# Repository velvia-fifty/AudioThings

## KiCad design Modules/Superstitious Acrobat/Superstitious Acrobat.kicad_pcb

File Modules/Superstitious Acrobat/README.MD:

# Superstitious Acrobat (and friends)

How many multiples give you the freedom to configure them how you want? OK but do they have *range*? I'm talking 1:13 to 14:0 range, how many 0 port multiples do you even have right now!?

## What problem are you trying to solve?

Consider the lede buried; I wanted a pair of FX loops and a compact way to shove a **FUCKTON** of signals into them. I also want the ability to touch those signals, not inappropriately but in the kind of way that garners stern looks of disapproval.

### Superstitious Acrobat

The first module is incredibly dense, your uncle's friend Dave from Facebook dense, A pair of 7 Stereo Jacks that you can slice, dice, and turn tricks with dense. Sure, you have to lay down solder blobs, and sure, you might have to think before you plug, but consider this:

Take a stereo signal, now give me two copies of that, and then a pair of each channel on the tip. Then take a second mono signal, split that six ways, and maybe throw the right channel of the other signal on the right side of half of those.

Why would you need to do that? 🤷‍♀️, but now you can.

### Midnight Gymnast

Wanna see me do some unorthodox splits?

Fill me up with a two pairs of stereo jacks (that's eight signals if you've lost count) and flip and twist until I make the sounds you like. Flip between each half of each pair, then blend each channel of those jacks.

Did this description need to be so passive aggressively sexual? 🍆💦☔️

### Full Send

Oh right, the FX loops, did I mention that there's a flat-flex cable so you can route the multiple right to it, or whatever - the interface port is standardized... 'n junk.

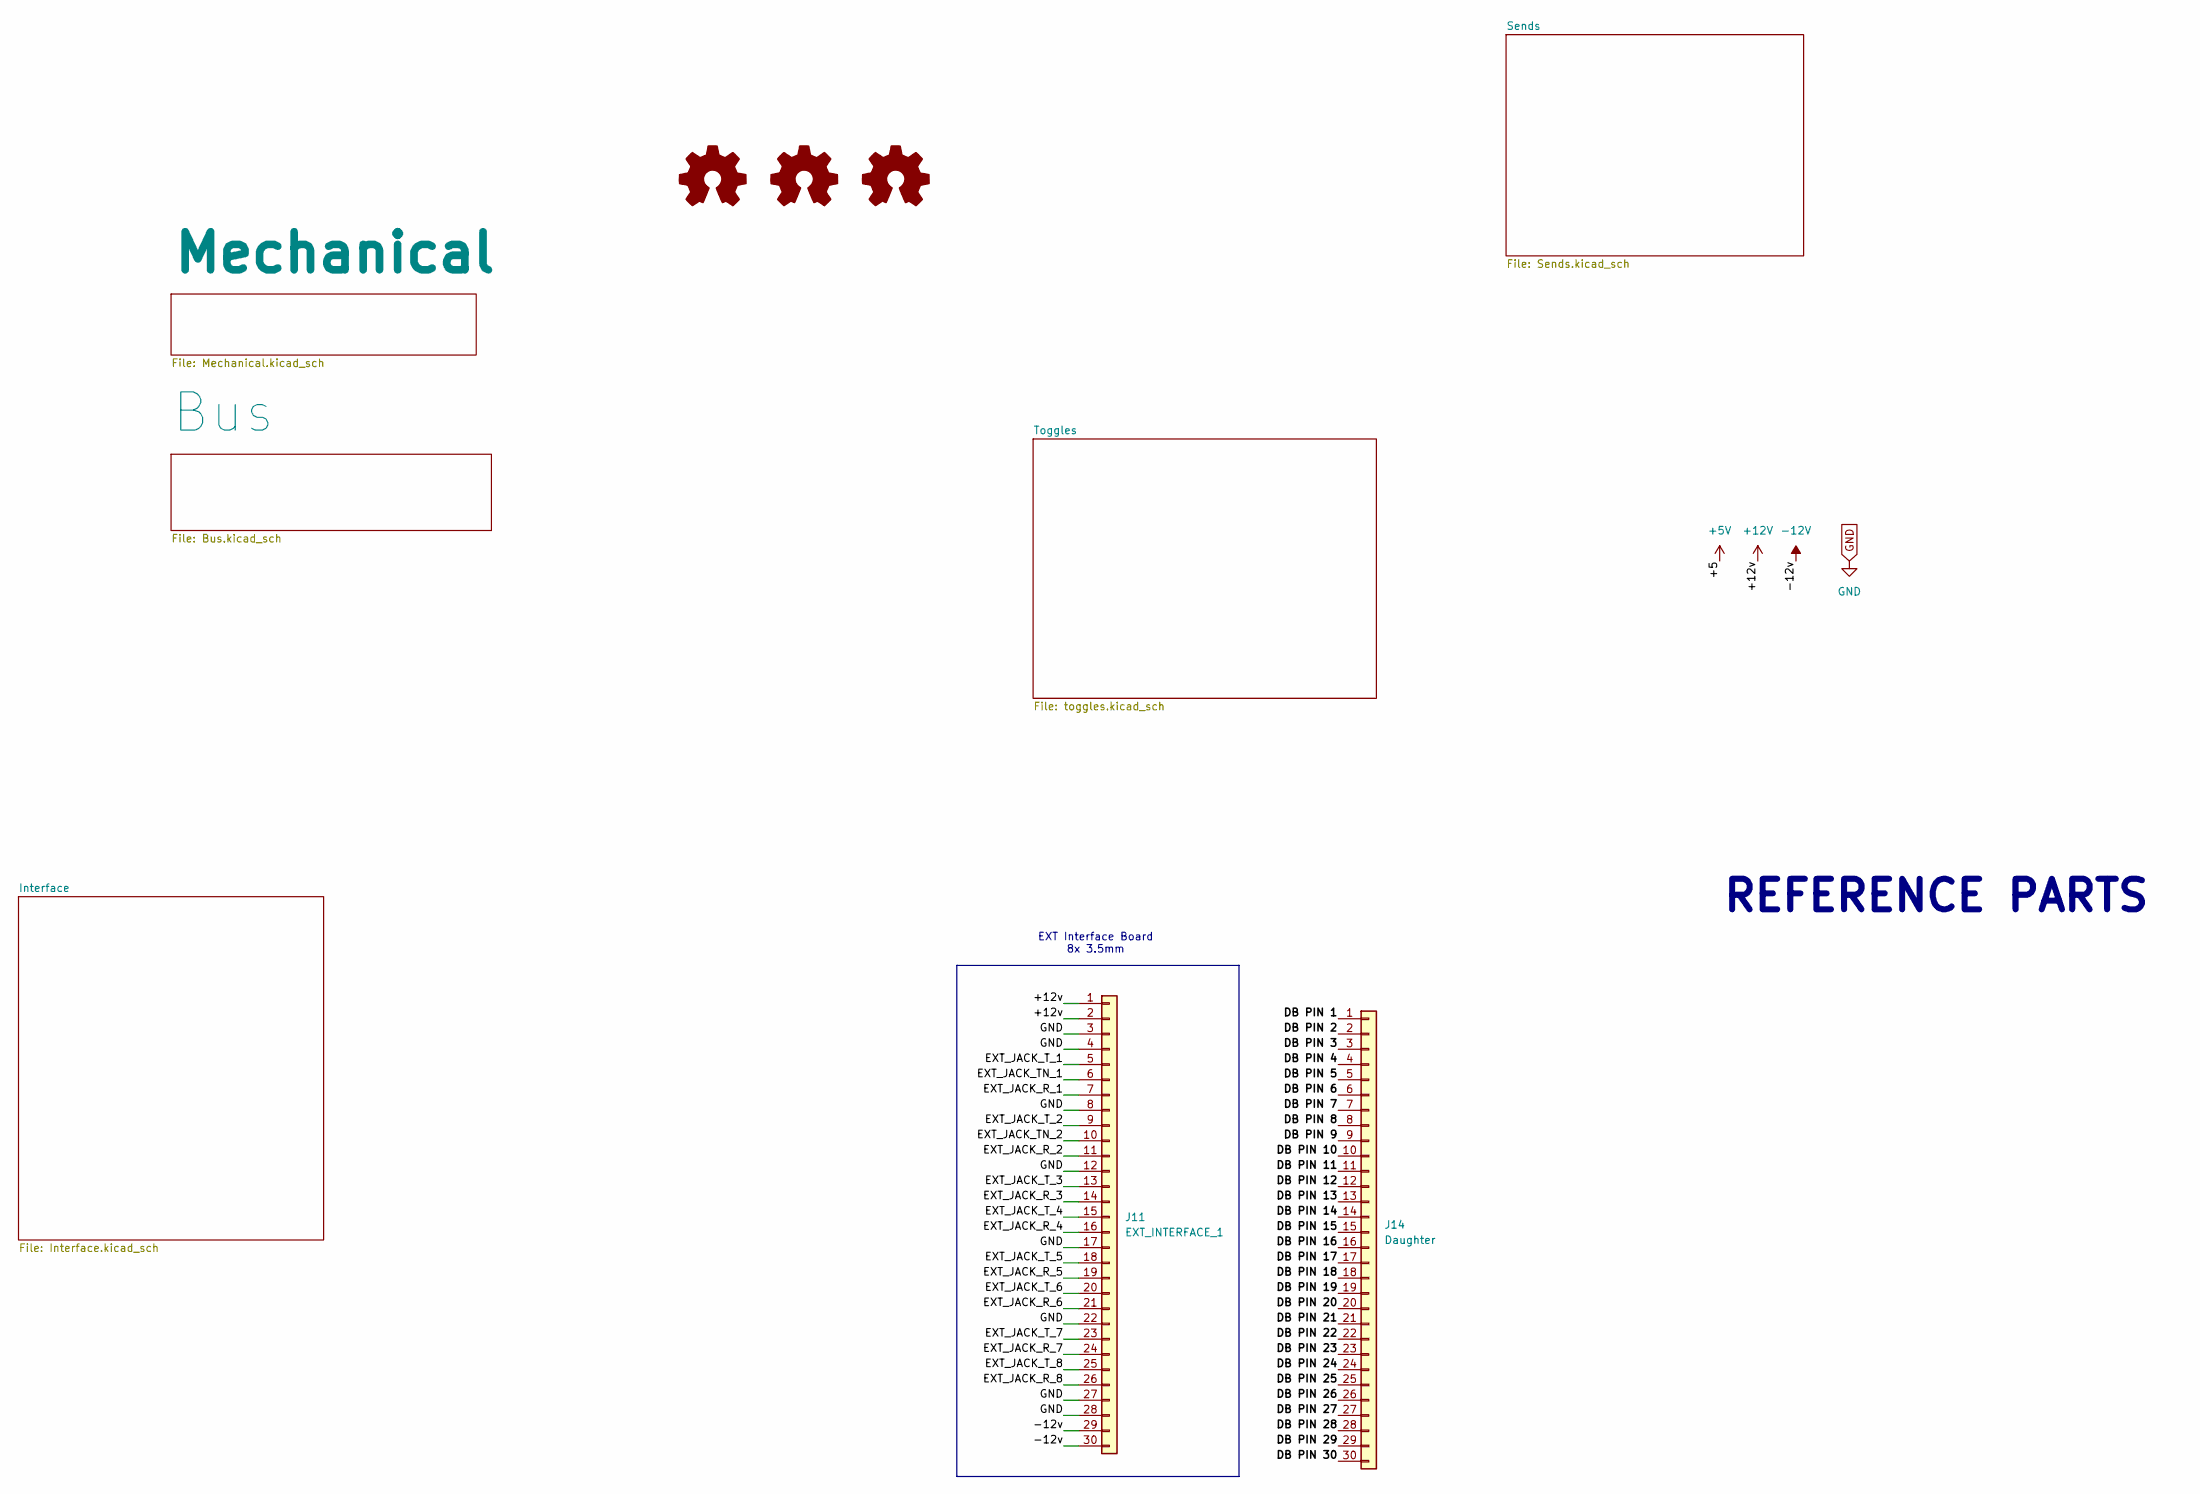
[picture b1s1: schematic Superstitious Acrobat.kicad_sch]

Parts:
J11: EXT_INTERFACE_1; AMPHENOL_SFV30R-4STE1HLF - FFC - 30 RA
J14: Daughter; AMPHENOL_SFV30R-4STE1HLF - FFC - 30 RA

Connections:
+12V: J11.1, J11.2
-12V: J11.29, J11.30
/EXT_JACK_R_1: J11.7
/EXT_JACK_R_2: J11.11
/EXT_JACK_R_3: J11.14
/EXT_JACK_R_4: J11.16
/EXT_JACK_R_5: J11.19
/EXT_JACK_R_6: J11.21
/EXT_JACK_R_7: J11.24
/EXT_JACK_R_8: J11.26
/EXT_JACK_TN_1: J11.6
/EXT_JACK_TN_2: J11.10
/EXT_JACK_T_1: J11.5
/EXT_JACK_T_2: J11.9
/EXT_JACK_T_3: J11.13
/EXT_JACK_T_4: J11.15
/EXT_JACK_T_5: J11.18
/EXT_JACK_T_6: J11.20
/EXT_JACK_T_7: J11.23
/EXT_JACK_T_8: J11.25
GND: J11.3, J11.4, J11.8, J11.12, J11.17, J11.22, J11.27, J11.28; also elsewhere on the board

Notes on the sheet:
REFERENCE PARTS
EXT Interface Board 8x 3.5mm

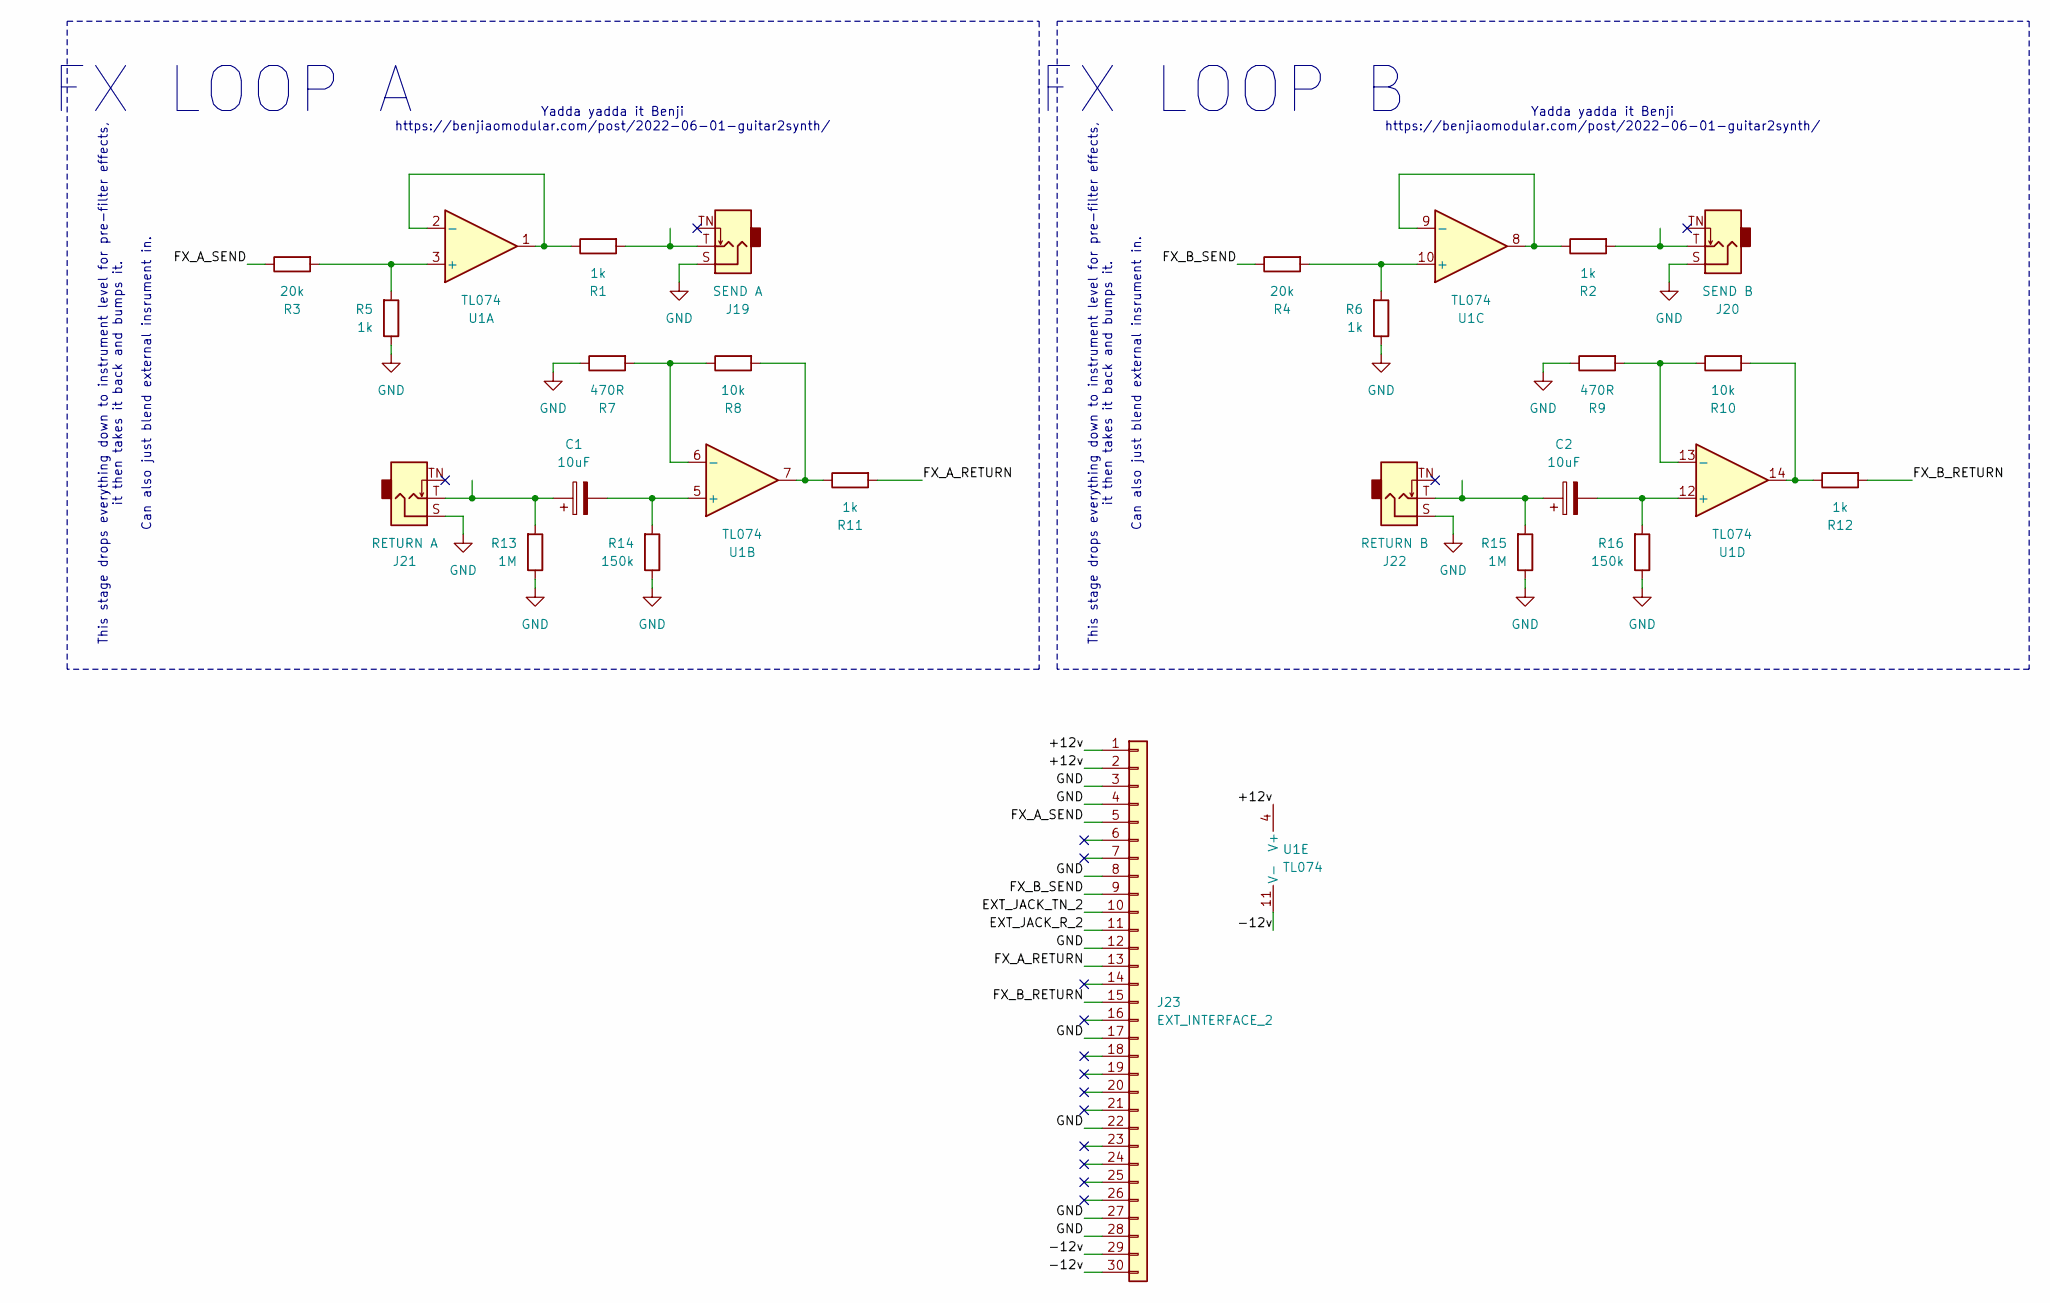
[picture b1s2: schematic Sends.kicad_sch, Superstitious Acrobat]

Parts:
C1, C2: 10uF; CP_Elec_5x5.4
J19: SEND A; Quarter Inch
J20: SEND B; Quarter Inch
J21: RETURN A; Quarter Inch
J22: RETURN B; Quarter Inch
J23: EXT_INTERFACE_2; AMPHENOL_SFV30R-4STE1HLF - FFC - 30 RA
R1, R2, R5, R6, R11, R12: 1k; R_0805_2012Metric_Pad1.20x1.40mm_HandSolder
R3, R4: 20k; R_0805_2012Metric_Pad1.20x1.40mm_HandSolder
R7, R9: 470R; R_0805_2012Metric_Pad1.20x1.40mm_HandSolder
R8, R10: 10k; R_0805_2012Metric_Pad1.20x1.40mm_HandSolder
R13, R15: 1M; R_0805_2012Metric_Pad1.20x1.40mm_HandSolder
R14, R16: 150k; R_0805_2012Metric_Pad1.20x1.40mm_HandSolder
U1: TL074; TSSOP-14_4.4x5mm_P0.65mm

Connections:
/Sends/+12v: J23.1, J23.2, U1.4 (V+)
/Sends/-12v: J23.29, J23.30, U1.11 (V-)
/Sends/EXT_JACK_R_2: J23.11
/Sends/EXT_JACK_TN_2: J23.10
/Sends/FX_A_RETURN: J23.13, R11.2
/Sends/FX_A_SEND: J23.5, R3.1
/Sends/FX_B_RETURN: J23.15, R12.2
/Sends/FX_B_SEND: J23.9, R4.1
GND: J19.S, J20.S, J21.S, J22.S, J23.3, J23.4, J23.8, J23.12, J23.17, J23.22, J23.27, J23.28, R5.1, R6.1, R7.1, R9.1, R13.1, R14.1, R15.1, R16.1; also elsewhere on the board
unnamed: C1.1, J21.T, R13.2
unnamed: C2.1, J22.T, R15.2
unnamed: J19.T, R1.2
unnamed: J20.T, R2.2
unnamed: R10.2, R12.1, U1.14
unnamed: R8.2, R11.1, U1.7
unnamed: R3.2, R5.2, U1.3 (+)
unnamed: R1.1, U1.1, U1.2 (-)
unnamed: C1.2, R14.2, U1.5 (+)
unnamed: R7.2, R8.1, U1.6 (-)
unnamed: R4.2, R6.2, U1.10 (+)
unnamed: R2.1, U1.8, U1.9 (-)
unnamed: C2.2, R16.2, U1.12 (+)
unnamed: R9.2, R10.1, U1.13 (-)

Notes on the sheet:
FX LOOP B
Yadda yadda it Benji https://benjiaomodular.com/post/2022-06-01-guitar2synth/
FX LOOP A
This stage drops everything down to instrument level for pre-filter effects, it then takes it back and bumps it. Can also just blend external insrument in.

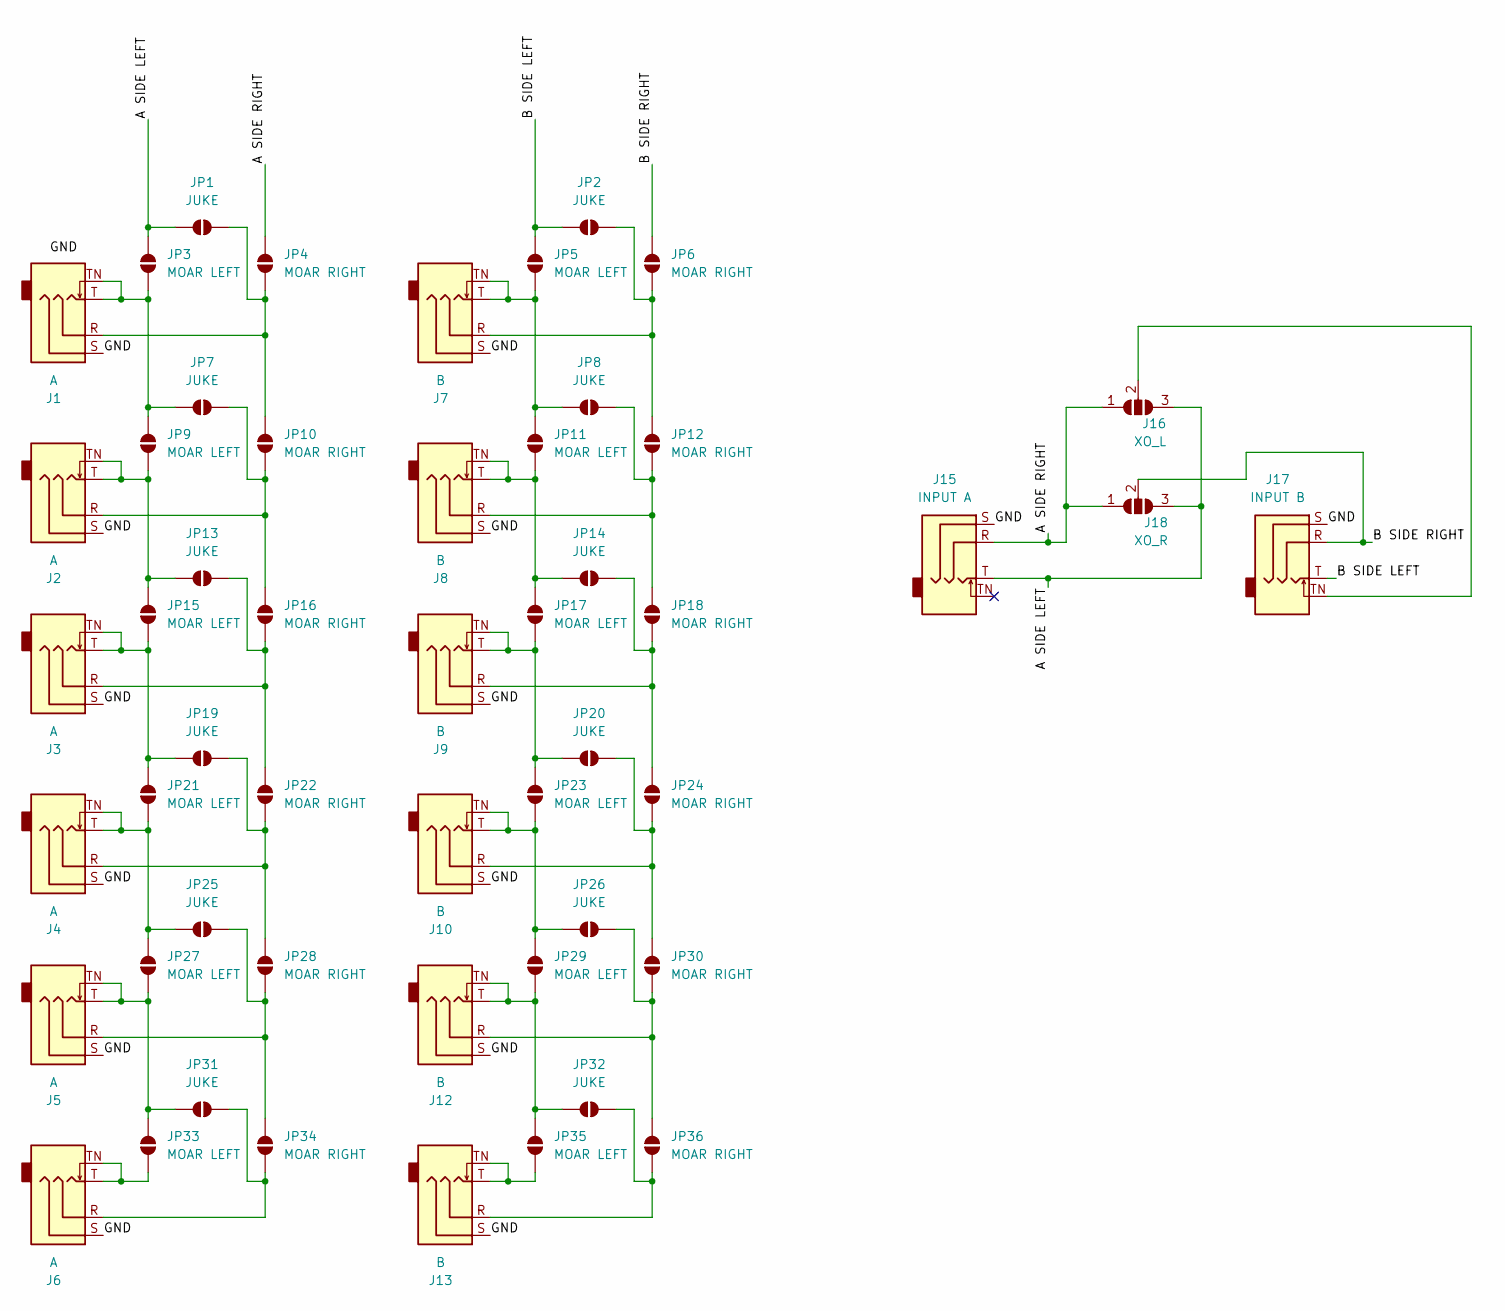
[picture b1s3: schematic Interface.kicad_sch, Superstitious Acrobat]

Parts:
J1, J2, J3, J4, J5, J6: A; SMD_STEREO_CUI_SJ-3524-SMT_Horizontal
J7, J8, J9, J10, J12, J13: B; SMD_STEREO_CUI_SJ-3524-SMT_Horizontal
J15: INPUT A; SMD_STEREO_CUI_SJ-3524-SMT_Horizontal
J16: XO_L; SolderJumper-3_P2.0mm_Open_TrianglePad1.0x1.5mm
J17: INPUT B; SMD_STEREO_CUI_SJ-3524-SMT_Horizontal
J18: XO_R; SolderJumper-3_P2.0mm_Open_TrianglePad1.0x1.5mm
JP1, JP2, JP7, JP8, JP13, JP14, JP19, JP20, JP25, JP26, JP31, JP32: JUKE; SolderJumper-2_P1.3mm_Open_TrianglePad1.0x1.5mm
JP3, JP5, JP9, JP11, JP15, JP17, JP21, JP23, JP27, JP29, JP33, JP35: MOAR LEFT; SolderJumper-2_P1.3mm_Open_TrianglePad1.0x1.5mm
JP4, JP6, JP10, JP12, JP16, JP18, JP22, JP24, JP28, JP30, JP34, JP36: MOAR RIGHT; SolderJumper-2_P1.3mm_Open_TrianglePad1.0x1.5mm

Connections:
/Interface/A SIDE LEFT: J15.T, J16.3 (B), J18.3 (B), JP1.2 (B), JP3.2 (B)
/Interface/A SIDE RIGHT: J15.R, J16.1 (A), J18.1 (A), JP4.2 (B)
/Interface/B SIDE LEFT: J17.T, JP2.2 (B), JP5.2 (B)
/Interface/B SIDE RIGHT: J17.R, J18.2 (C), JP6.2 (B)
/Interface/GND: J1.S, J2.S, J3.S, J4.S, J5.S, J6.S, J7.S, J8.S, J9.S, J10.S, J12.S, J13.S, J15.S, J17.S
unnamed: J16.2 (C), J17.TN
unnamed: J1.R, JP1.1 (A), JP4.1 (A), JP10.2 (B)
unnamed: J1.T, J1.TN, JP3.1 (A), JP7.2 (B), JP9.2 (B)
unnamed: J2.R, JP7.1 (A), JP10.1 (A), JP16.2 (B)
unnamed: J8.T, J8.TN, JP11.1 (A), JP14.2 (B), JP17.2 (B)
unnamed: J7.T, J7.TN, JP5.1 (A), JP8.2 (B), JP11.2 (B)
unnamed: J8.R, JP8.1 (A), JP12.1 (A), JP18.2 (B)
unnamed: J7.R, JP2.1 (A), JP6.1 (A), JP12.2 (B)
unnamed: J3.R, JP13.1 (A), JP16.1 (A), JP22.2 (B)
unnamed: J2.T, J2.TN, JP9.1 (A), JP13.2 (B), JP15.2 (B)
unnamed: J9.R, JP14.1 (A), JP18.1 (A), JP24.2 (B)
unnamed: J3.T, J3.TN, JP15.1 (A), JP19.2 (B), JP21.2 (B)
unnamed: J9.T, J9.TN, JP17.1 (A), JP20.2 (B), JP23.2 (B)
unnamed: J4.R, JP19.1 (A), JP22.1 (A), JP28.2 (B)
unnamed: J10.R, JP20.1 (A), JP24.1 (A), JP30.2 (B)
unnamed: J4.T, J4.TN, JP21.1 (A), JP25.2 (B), JP27.2 (B)
unnamed: J10.T, J10.TN, JP23.1 (A), JP26.2 (B), JP29.2 (B)
unnamed: J5.R, JP25.1 (A), JP28.1 (A), JP34.2 (B)
unnamed: J12.R, JP26.1 (A), JP30.1 (A), JP36.2 (B)
unnamed: J5.T, J5.TN, JP27.1 (A), JP31.2 (B), JP33.2 (B)
unnamed: J12.T, J12.TN, JP29.1 (A), JP32.2 (B), JP35.2 (B)
unnamed: J6.R, JP31.1 (A), JP34.1 (A)
unnamed: J13.R, JP32.1 (A), JP36.1 (A)
unnamed: J6.T, J6.TN, JP33.1 (A)
unnamed: J13.T, J13.TN, JP35.1 (A)

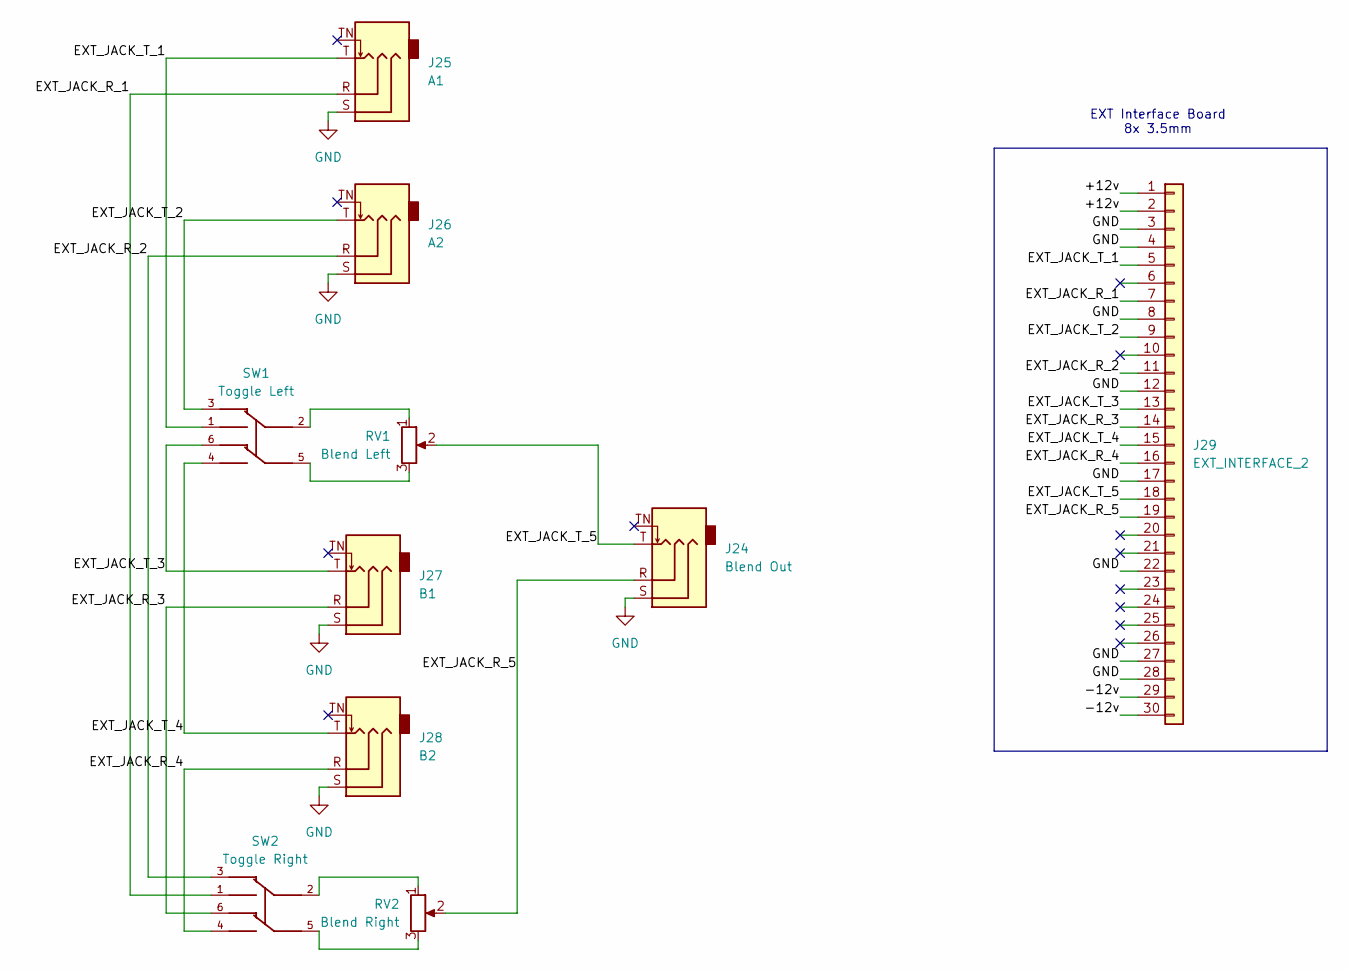
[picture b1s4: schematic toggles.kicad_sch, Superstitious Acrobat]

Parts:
J24: Blend Out; SMD_STEREO_CUI_SJ-3524-SMT_Horizontal
J25: A1; SMD_STEREO_CUI_SJ-3524-SMT_Horizontal
J26: A2; SMD_STEREO_CUI_SJ-3524-SMT_Horizontal
J27: B1; SMD_STEREO_CUI_SJ-3524-SMT_Horizontal
J28: B2; SMD_STEREO_CUI_SJ-3524-SMT_Horizontal
J29: EXT_INTERFACE_2; AMPHENOL_SFV30R-4STE1HLF - FFC - 30 RA
RV1: Blend Left; Potentiometer_Bourns_PTV09A-2_Single_Horizontal
RV2: Blend Right; Potentiometer_Bourns_PTV09A-2_Single_Horizontal
SW1: Toggle Left; DPDT Micro SW_1825138-7; PARTREV A5
SW2: Toggle Right; DPDT Micro SW_1825138-7; PARTREV A5

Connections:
/Toggles/+12v: J29.1, J29.2
/Toggles/-12v: J29.29, J29.30
/Toggles/EXT_JACK_R_1: J25.R, J29.7, SW2.1
/Toggles/EXT_JACK_R_2: J26.R, J29.11, SW2.3
/Toggles/EXT_JACK_R_3: J27.R, J29.14, SW2.6
/Toggles/EXT_JACK_R_4: J28.R, J29.16, SW2.4
/Toggles/EXT_JACK_R_5: J24.R, J29.19, RV2.2
/Toggles/EXT_JACK_T_1: J25.T, J29.5, SW1.1
/Toggles/EXT_JACK_T_2: J26.T, J29.9, SW1.3
/Toggles/EXT_JACK_T_3: J27.T, J29.13, SW1.6
/Toggles/EXT_JACK_T_4: J28.T, J29.15, SW1.4
/Toggles/EXT_JACK_T_5: J24.T, J29.18, RV1.2
GND: J24.S, J25.S, J26.S, J27.S, J28.S, J29.3, J29.4, J29.8, J29.12, J29.17, J29.22, J29.27, J29.28; also elsewhere on the board
unnamed: RV1.1, SW1.2
unnamed: RV1.3, SW1.5
unnamed: RV2.1, SW2.2
unnamed: RV2.3, SW2.5

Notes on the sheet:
EXT Interface Board 8x 3.5mm

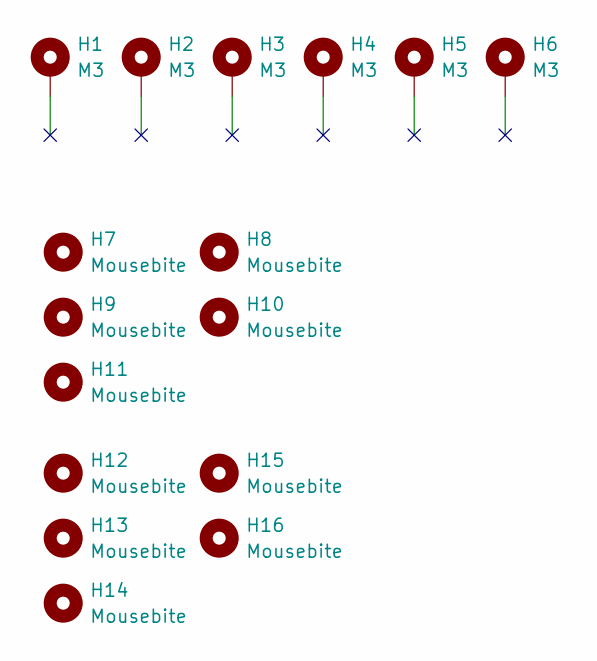
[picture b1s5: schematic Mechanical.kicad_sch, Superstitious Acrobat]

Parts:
H1, H2, H3, H4, H5, H6: M3; MountingHole_3.2mm_M3_DIN965_Pad
H7, H8, H9, H10, H11, H12, H13, H14, H15, H16: Mousebite; mouse-bite-2mm-slot

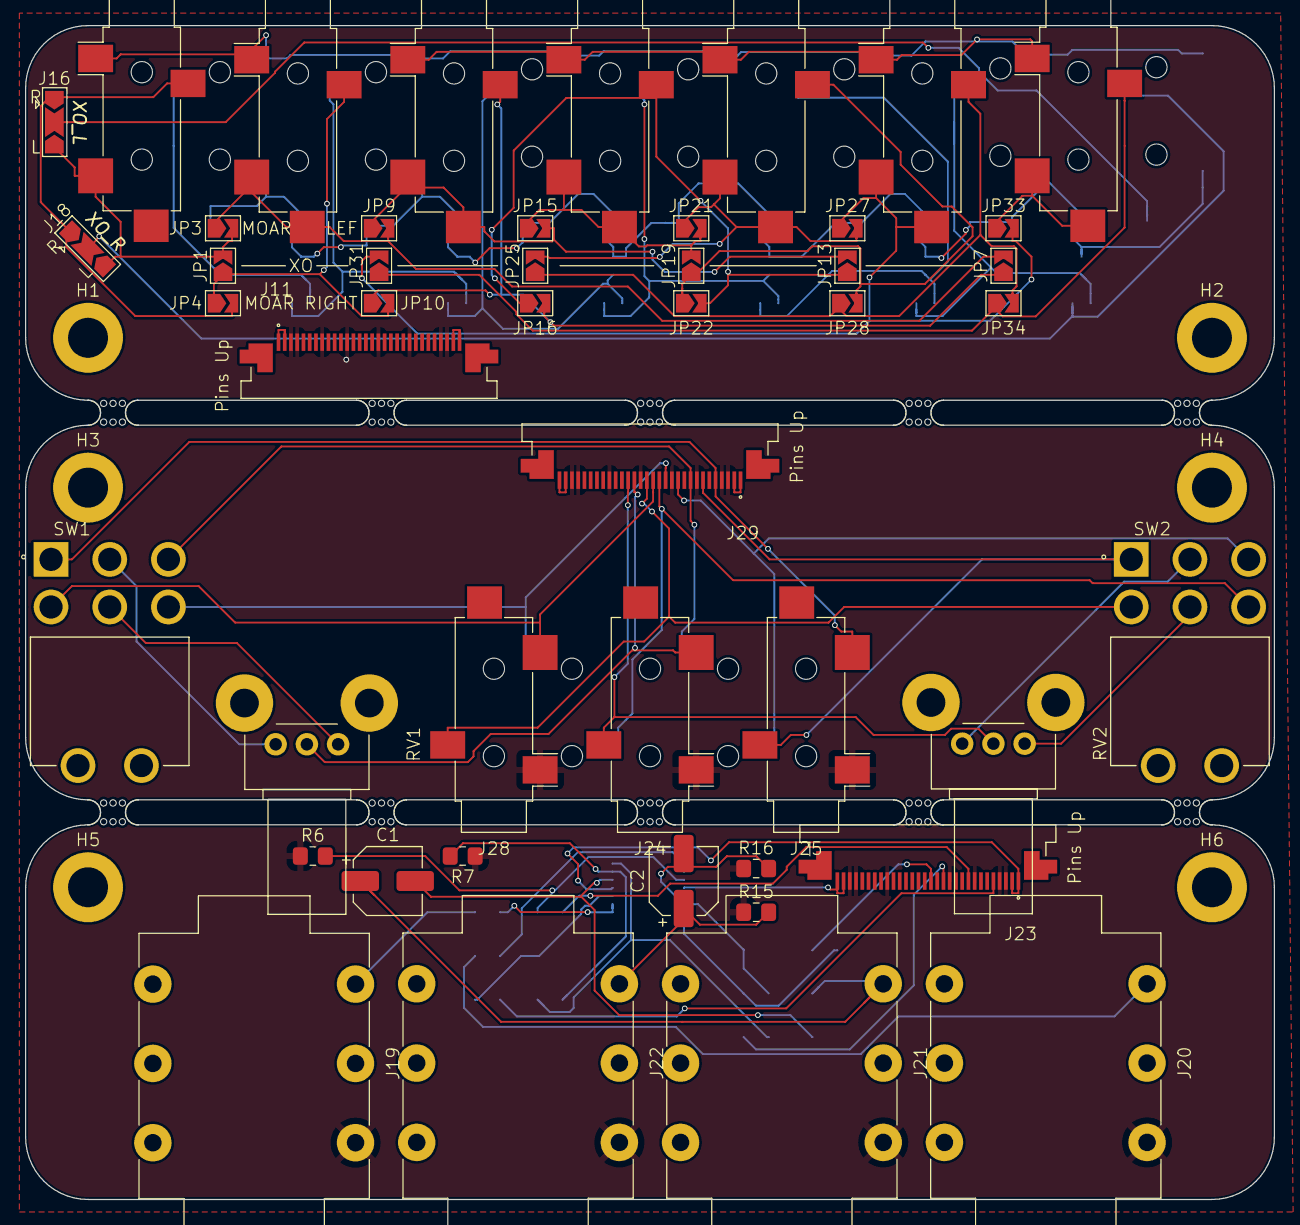
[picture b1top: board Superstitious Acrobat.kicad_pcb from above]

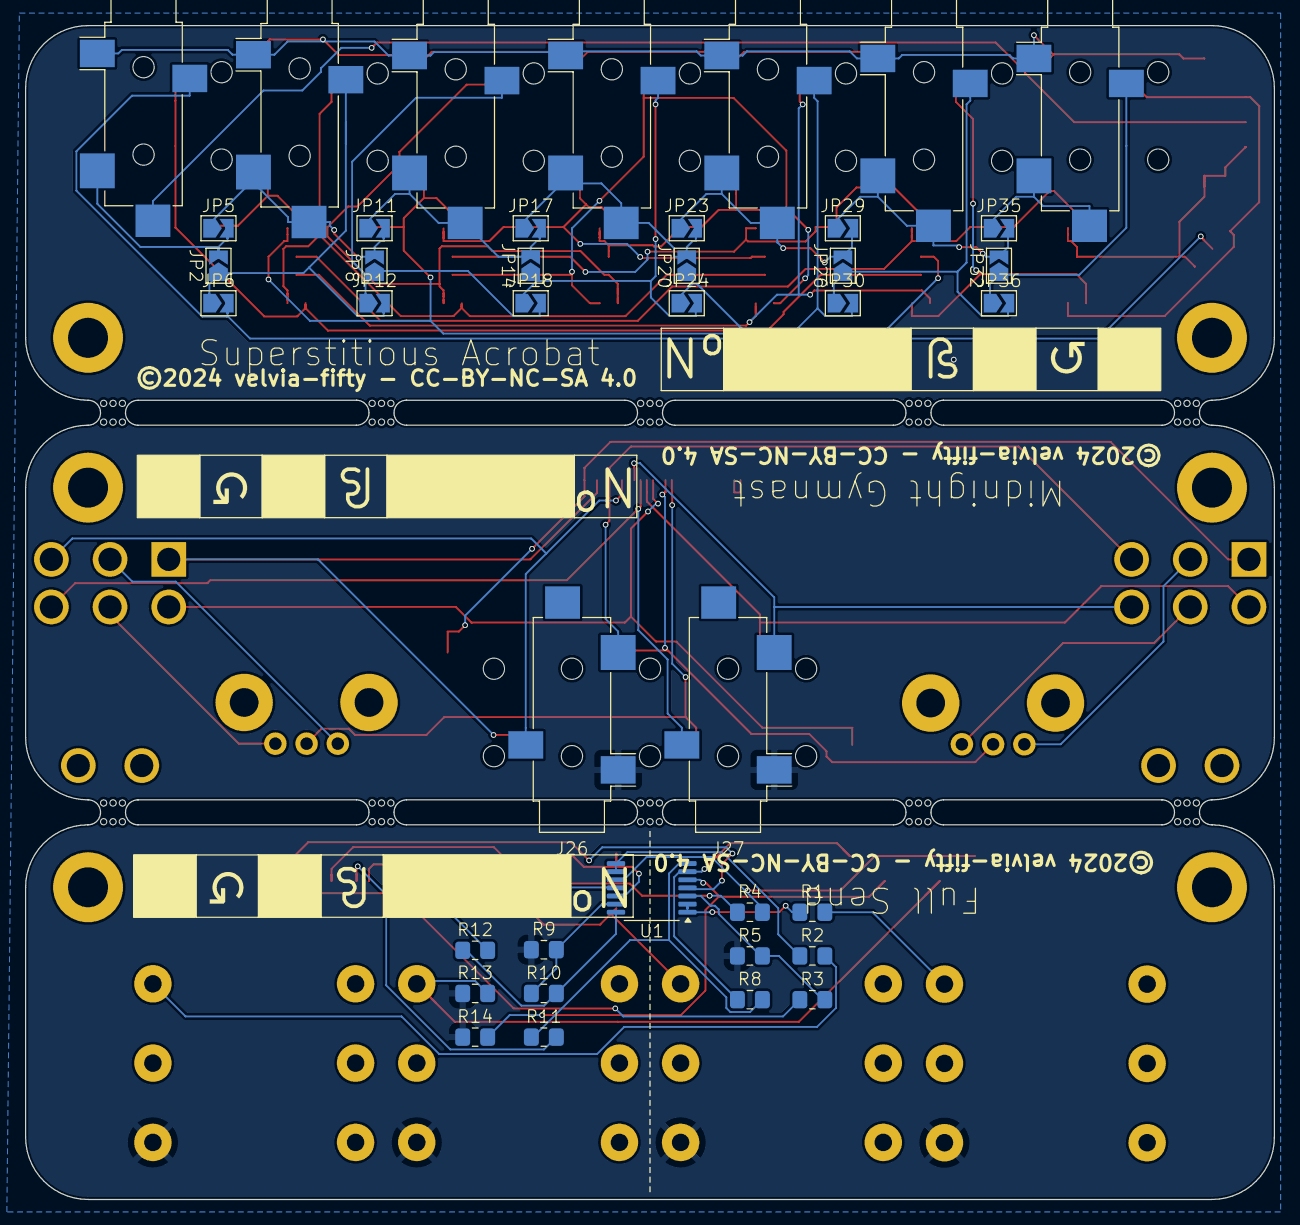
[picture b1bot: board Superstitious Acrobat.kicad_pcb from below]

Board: 2 copper layers, 100.0 x 94.0 mm, 103 parts (40 on the bottom side), 69 nets.

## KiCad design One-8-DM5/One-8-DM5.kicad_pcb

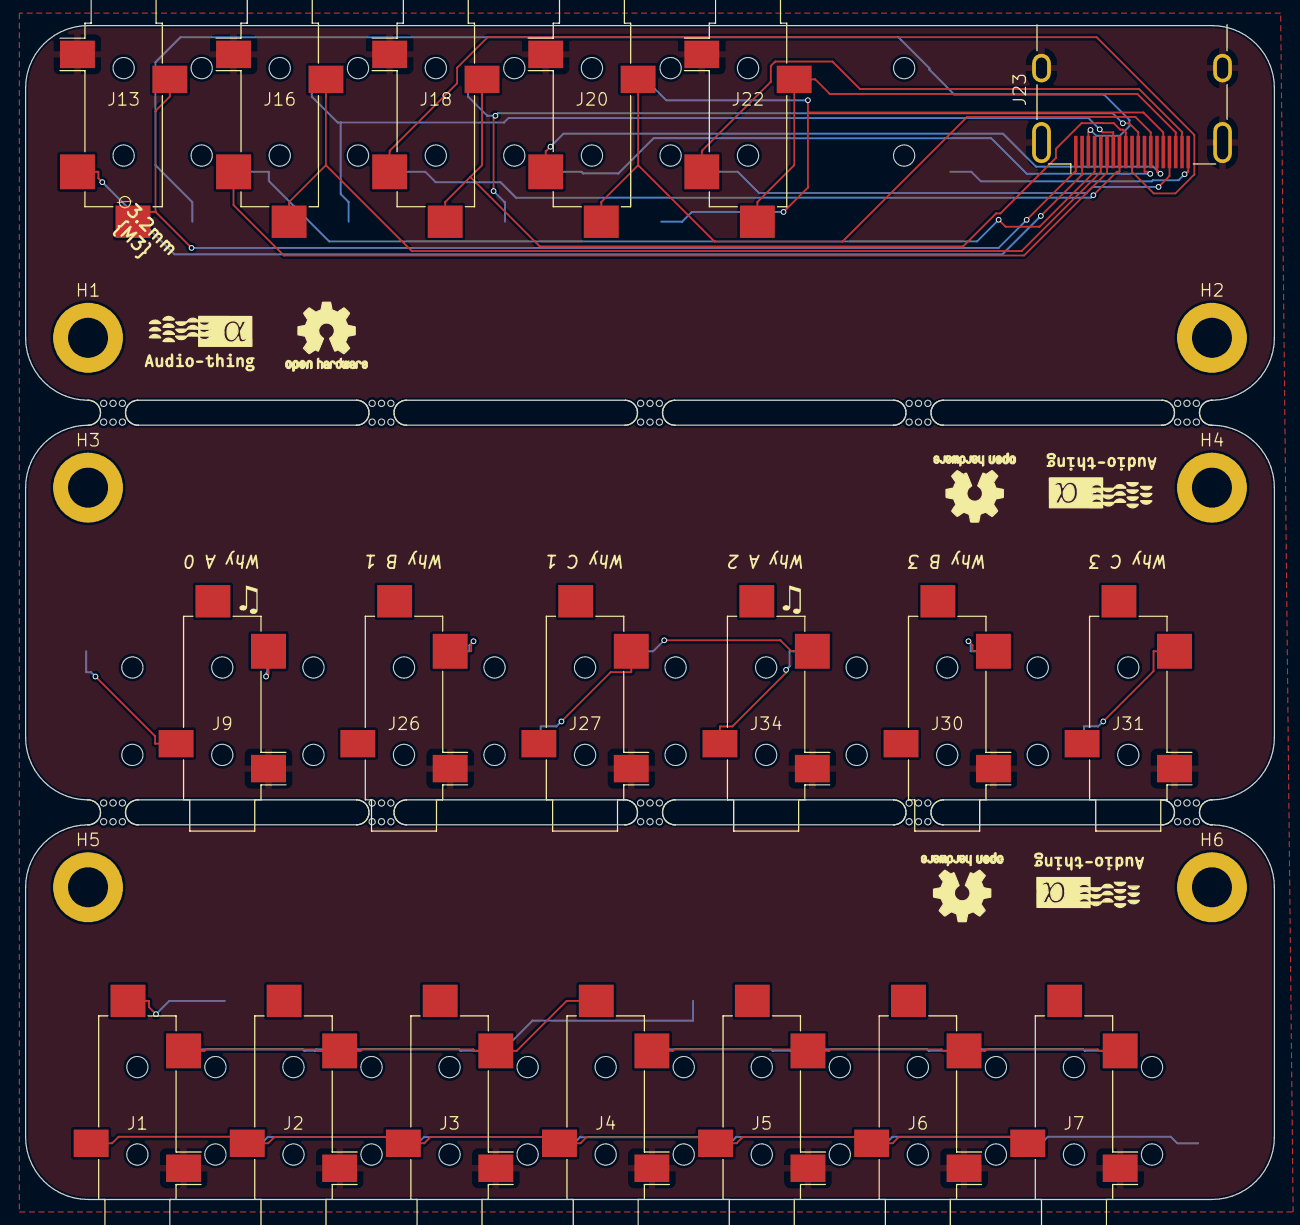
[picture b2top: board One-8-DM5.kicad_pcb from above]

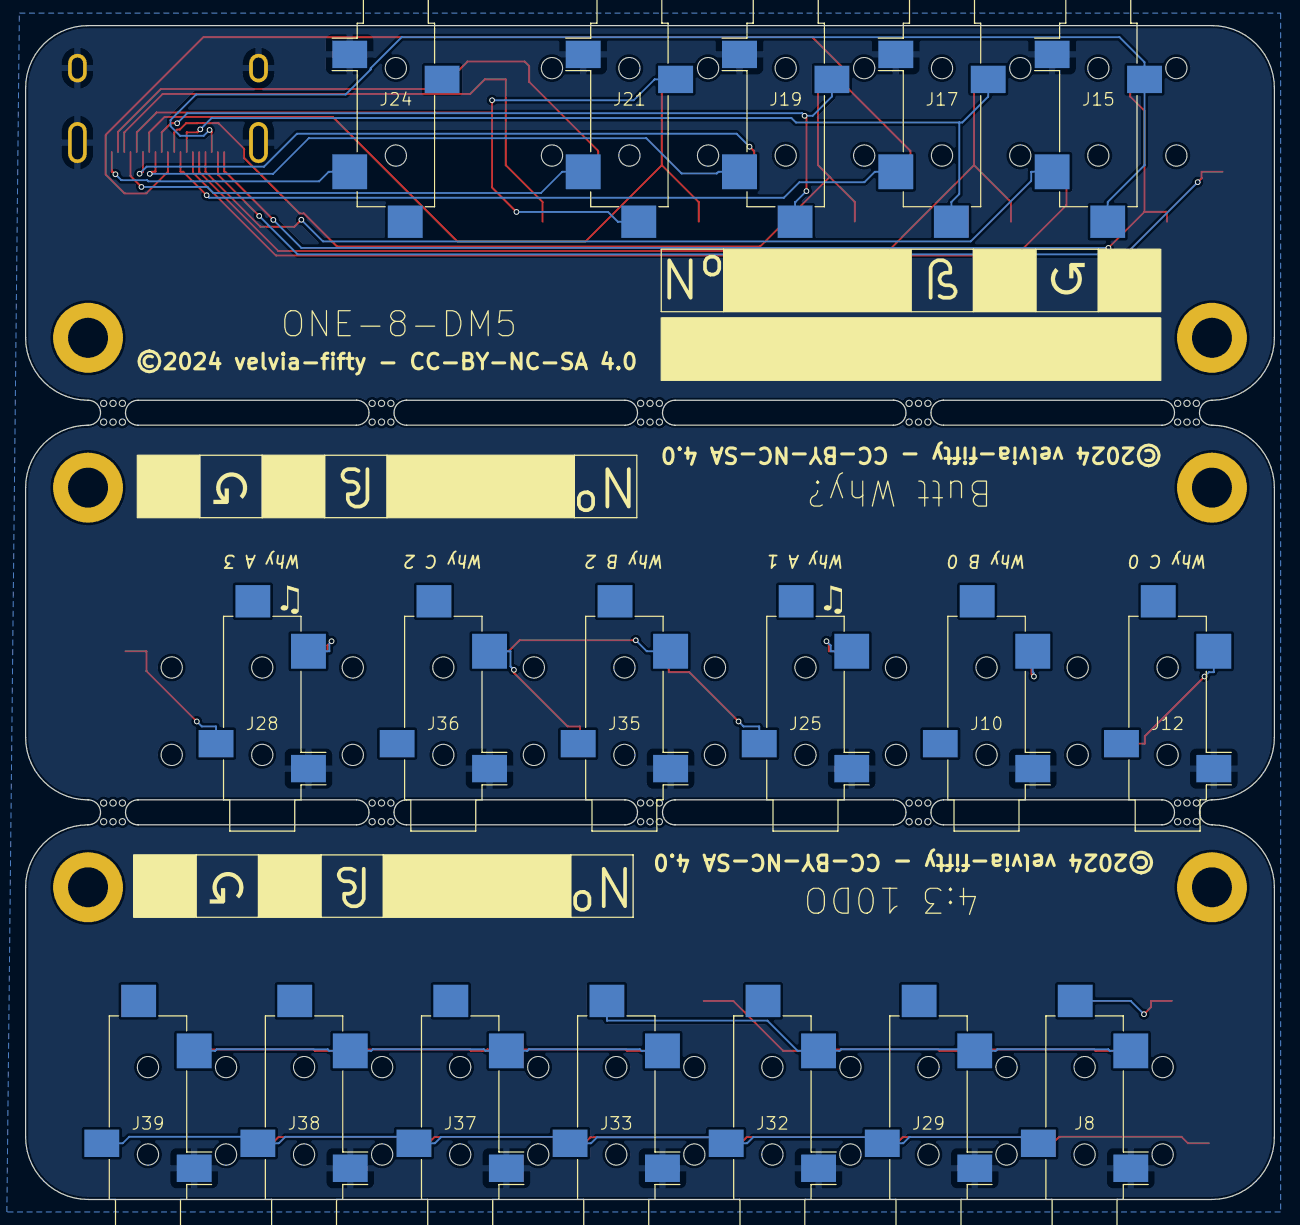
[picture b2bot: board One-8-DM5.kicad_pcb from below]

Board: 2 copper layers, 100.0 x 94.0 mm, 59 parts (18 on the bottom side), 35 nets.

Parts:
G1, G3, G5: LOGO; at-logo
G2, G4, G6: OSHW-Logo2_7.3x6mm_SilkScreen
H1, H2, H3, H4, H5, H6: M3; MountingHole_3.2mm_M3_DIN965_Pad
H7, H8, H9, H10, H11, H12, H13, H14, H15, H16: Mousebite; mouse-bite-2mm-slot
J1, J2, J3: ALPHA; Jack_3.5mm_CUI_SJ-3524-SMT_Horizontal
J4: BETA; Jack_3.5mm_CUI_SJ-3524-SMT_Horizontal
J5, J6, J7: A/B; Jack_3.5mm_CUI_SJ-3524-SMT_Horizontal
J8: A/GAMMA; Jack_3.5mm_CUI_SJ-3524-SMT_Horizontal
J9: Why A 0; Jack_3.5mm_CUI_SJ-3524-SMT_Horizontal
J10: Why B 0; Jack_3.5mm_CUI_SJ-3524-SMT_Horizontal
J12: Why C 0; Jack_3.5mm_CUI_SJ-3524-SMT_Horizontal
J13: Stereo 0; Jack_3.5mm_CUI_SJ-3524-SMT_Horizontal
J15: Stereo 1; Jack_3.5mm_CUI_SJ-3524-SMT_Horizontal
J16: Stereo 2; Jack_3.5mm_CUI_SJ-3524-SMT_Horizontal
J17: Stereo 3; Jack_3.5mm_CUI_SJ-3524-SMT_Horizontal
J18: Stereo 4; Jack_3.5mm_CUI_SJ-3524-SMT_Horizontal
J19: Stereo 5; Jack_3.5mm_CUI_SJ-3524-SMT_Horizontal
J20: Stereo 6; Jack_3.5mm_CUI_SJ-3524-SMT_Horizontal
J21: Stereo 7; Jack_3.5mm_CUI_SJ-3524-SMT_Horizontal
J22: Stereo 8; Jack_3.5mm_CUI_SJ-3524-SMT_Horizontal
J23: HDMI; HDMI_A_Molex_208658-1001_Horizontal
J24: Mono; Jack_3.5mm_CUI_SJ-3524-SMT_Horizontal
J25: Why A 1; Jack_3.5mm_CUI_SJ-3524-SMT_Horizontal
J26: Why B 1; Jack_3.5mm_CUI_SJ-3524-SMT_Horizontal
J27: Why C 1; Jack_3.5mm_CUI_SJ-3524-SMT_Horizontal
J28: Why A 3; Jack_3.5mm_CUI_SJ-3524-SMT_Horizontal
J29, J32: GAMMA; Jack_3.5mm_CUI_SJ-3524-SMT_Horizontal
J30: Why B 3; Jack_3.5mm_CUI_SJ-3524-SMT_Horizontal
J31: Why C 3; Jack_3.5mm_CUI_SJ-3524-SMT_Horizontal
J33: DELTA; Jack_3.5mm_CUI_SJ-3524-SMT_Horizontal
J34: Why A 2; Jack_3.5mm_CUI_SJ-3524-SMT_Horizontal
J35: Why B 2; Jack_3.5mm_CUI_SJ-3524-SMT_Horizontal
J36: Why C 2; Jack_3.5mm_CUI_SJ-3524-SMT_Horizontal
J37, J38, J39: C/D; Jack_3.5mm_CUI_SJ-3524-SMT_Horizontal

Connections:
/Ring 0: J13.R, J13.TN, J23.1
/Ring 1: J15.R, J15.TN, J23.3
/Ring 2: J16.R, J16.TN, J23.5
/Ring 3: J17.R, J17.TN, J23.7
/Ring 4: J18.R, J18.TN, J23.9
/Ring 5: J19.R, J19.TN, J23.11
/Ring 6: J20.R, J20.TN, J23.13
/Ring 7: J21.R, J21.TN, J23.15
/Ring 8: J22.R, J22.TN, J23.17
/TIP 0: J13.T, J23.2
/TIP 1: J15.T, J23.4
/TIP 2: J16.T, J23.6
/TIP 3: J17.T, J23.8
/TIP 4: J18.T, J23.10
/TIP 5: J19.T, J23.12
/TIP 6: J20.T, J23.14
/TIP 7: J21.T, J23.16
/TIP 8: J22.T, J23.18
/TIP 9: J23.19, J24.T
GND: J1.S, J2.S, J3.S, J4.S, J5.S, J6.S, J7.S, J8.S, J9.S, J10.S, J12.S, J13.S, J15.S, J16.S, J17.S, J18.S, J19.S, J20.S, J21.S, J22.S, J23.SH (Sheild), J24.S, J25.S, J26.S, J27.S, J28.S, J29.S, J30.S, J31.S, J32.S, J33.S, J34.S, J35.S, J36.S, J37.S, J38.S, J39.S
unnamed: J1.R, J2.R, J3.R, J4.R, J5.R, J6.R, J7.R
unnamed: J1.T, J2.T, J3.T, J4.TN
unnamed: J1.TN, J8.TN
unnamed: J4.T, J5.T, J6.T, J7.T
unnamed: J9.T, J10.T
unnamed: J9.R, J12.T
unnamed: J25.R, J27.T
unnamed: J25.T, J26.T
unnamed: J28.R, J31.T
unnamed: J28.T, J30.T
unnamed: J8.R, J29.R, J32.R, J33.R, J37.R, J38.R, J39.R
unnamed: J8.T, J29.T, J32.T, J33.TN
unnamed: J33.T, J37.T, J38.T, J39.T
unnamed: J34.R, J36.T
unnamed: J34.T, J35.T

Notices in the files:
Modules/Superstitious Acrobat/Superstitious Acrobat.kicad_pcb:
©2024 velvia-fifty - CC-BY-NC-SA 4.0
Workshop/AT-Template-Front Panel/AT-Template-Front Panel.kicad_pcb:
CC-BY-NC-SA 4.0
